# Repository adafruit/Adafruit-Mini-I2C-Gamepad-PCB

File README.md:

## Adafruit Mini I2C Gamepad with seesaw and STEMMA QT PCB

<a href="http://www.adafruit.com/products/5743"><br/>
Click here to purchase one from the Adafruit shop</a>

PCB files for the Adafruit Mini I2C Gamepad with seesaw and STEMMA QT. 

Format is EagleCAD schematic and board layout
* https://www.adafruit.com/product/5743

### Description

Make a game or robotic controller for any I2C microcontroller or microcomputer with this tiny gamepad breakout board. This design has a 2-axis thumb joystick and 6 momentary buttons (4 large and 2 small). The board communicates with your host microcontroller over I2C so it's easy to use and doesn't take up any of your precious analog or digital pins. There is also an optional interrupt pin that can alert your feather when a button has been pressed or released to free up processor time for other tasks.

You can use our Arduino library to control and read data with any compatible microcontroller. We also have CircuitPython/Python code for use with computers or single-board Linux boards.

To get you going fast, this board comes with a STEMMA QT connector, making them easy to interface with. The STEMMA QT connector is compatible with the SparkFun Qwiic I2C connectors. This allows you to make solderless connections between your development board and the gamepad or to chain it with a wide range of other sensors and accessories using a compatible cable and a 'hub' board. QT Cable is not included, but we have a variety in the shop.

This board features Adafruit seesaw technology - a custom programmed little helper microcontroller that takes the two analog inputs from the joystick, and 6 button inputs, and converts it into a pretty I2C interface. This I2C interface means you don't 'lose' any GPIO or analog inputs, and it works with any and all microcontrollers or microcomputers - even if they don't have an analog input for the thumbstick! 

If you have an I2C address conflict, or you want to connect more than one of these to a board, there are two address-select jumpers so you have 4 options of I2C addresses.

There's an optional IRQ (interrupt) line that you can use if you'd like the gamepad to let you know when a button has been pressed. Since its optional you will need to connect a separate wire for the IRQ line, or just leave it disconnected.

Comes with one assembled and programmed Gamepad, and some 0.1" header. If you aren't using Stemma QT cables, some soldering is required to attach the header for breadboarding.

### License

Adafruit invests time and resources providing this open source design, please support Adafruit and open-source hardware by purchasing products from [Adafruit](https://www.adafruit.com)!

Designed by Limor Fried/Ladyada for Adafruit Industries.

Creative Commons Attribution/Share-Alike, all text above must be included in any redistribution. 
See license.txt for additional details.

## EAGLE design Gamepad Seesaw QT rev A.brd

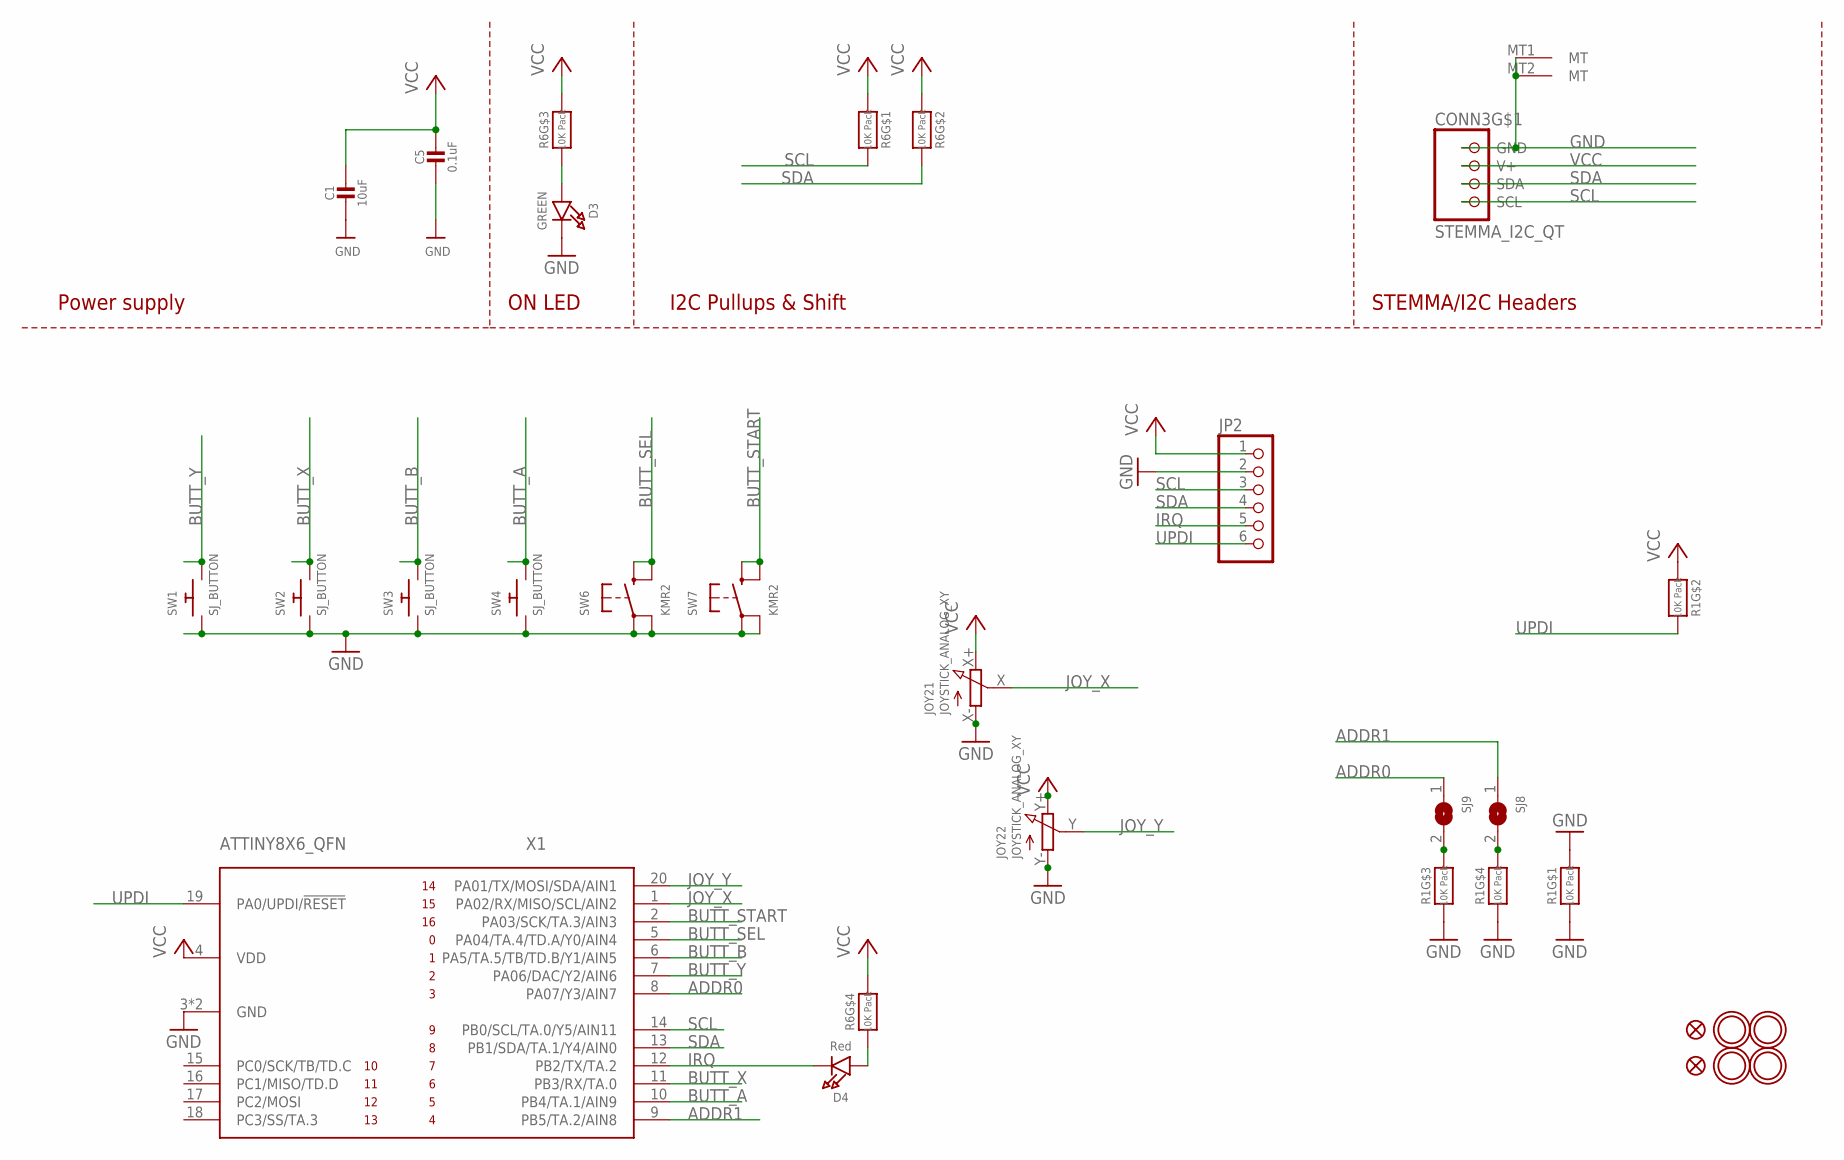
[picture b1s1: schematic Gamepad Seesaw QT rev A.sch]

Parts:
C1: 10uF; 0805-NO
C5: 0.1uF; 0603-NO
CONN3: STEMMA_I2C_QT; JST_SH4
D3: GREEN; CHIPLED_0603_NOOUTLINE
D4: Red; CHIPLED_0603_NOOUTLINE
FID1, FID2: FIDUCIAL_1MM
JOY2: JOYSTICK_ANALOG_XY; JOYSTICK_ANALOG_MINITHM
JP2: HEADER-1X6ROUND; 1X06_ROUND
R1, R6: 10K Pack; RESPACK_4X0603
SJ8, SJ9: SOLDERJUMPERCLOSED; SOLDERJUMPER_CLOSEDWIRE
SW1, SW2, SW3, SW4: SJ_BUTTON; PUSHBUTTON_SMD_SJ
SW6, SW7: KMR2; BTN_RKB2_4.6X2.8
U$1, U$2, U$3, U$4: MOUNTINGHOLE2.5; MOUNTINGHOLE_2.5_PLATED
X1: ATTINY8X6_QFN; QFN20_3MM

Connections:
ADDR0: SJ9.1, X1.8 (PA07/Y3/AIN7)
ADDR1: SJ8.1, X1.9 (PB5/TA.2/AIN8)
BUTT_A: SW4.P$2, X1.10 (PB4/TA.1/AIN9)
BUTT_B: SW3.P$2, X1.6 (PA5/TA.5/TB/TD.B/Y1/AIN5)
BUTT_SEL: SW6.B (S), SW6.B' (S1), X1.5 (PA04/TA.4/TD.A/Y0/AIN4)
BUTT_START: SW7.B (S), SW7.B' (S1), X1.2 (PA03/SCK/TA.3/AIN3)
BUTT_X: SW2.P$2, X1.11 (PB3/RX/TA.0)
BUTT_Y: SW1.P$2, X1.7 (PA06/DAC/Y2/AIN6)
GND: C1.2, C5.2, CONN3.1 (GND), CONN3.MT1 (MT), CONN3.MT2 (MT), D3.C, JOY2.X- (A), JOY2.Y- (A), JP2.2, R1.1, R1.3 (1), R1.4 (1), R1.8 (2), SW1.P$1, SW2.P$1, SW3.P$1, SW4.P$1, SW6.A, SW6.A' (P1), SW7.A, SW7.A' (P1), X1.3 (GND), X1.PAD (GND)
IRQ: D4.C, JP2.5, X1.12 (PB2/TX/TA.2)
JOY_X: JOY2.X (S), X1.1 (PA02/RX/MISO/SCL/AIN2)
JOY_Y: JOY2.Y (S), X1.20 (PA01/TX/MOSI/SDA/AIN1)
unnamed: D3.A, R6.3 (1)
unnamed: R1.6 (2), SJ9.2
unnamed: R1.5 (2), SJ8.2
unnamed: D4.A, R6.4 (1)
SCL: CONN3.4 (SCL), JP2.3, R6.8 (2), X1.14 (PB0/SCL/TA.0/Y5/AIN11)
SDA: CONN3.3 (SDA), JP2.4, R6.7 (2), X1.13 (PB1/SDA/TA.1/Y4/AIN0)
UPDI: JP2.6, R1.7 (2), X1.19 (PA0/UPDI/!RESET)
VCC: C1.1, C5.1, CONN3.2 (V+), JOY2.X+ (E), JOY2.Y+ (E), JP2.1, R1.2 (1), R6.1, R6.2 (1), R6.5 (2), R6.6 (2), X1.4 (VDD)

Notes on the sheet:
I2C Pullups & Shift
STEMMA/I2C Headers
ON LED
Power supply

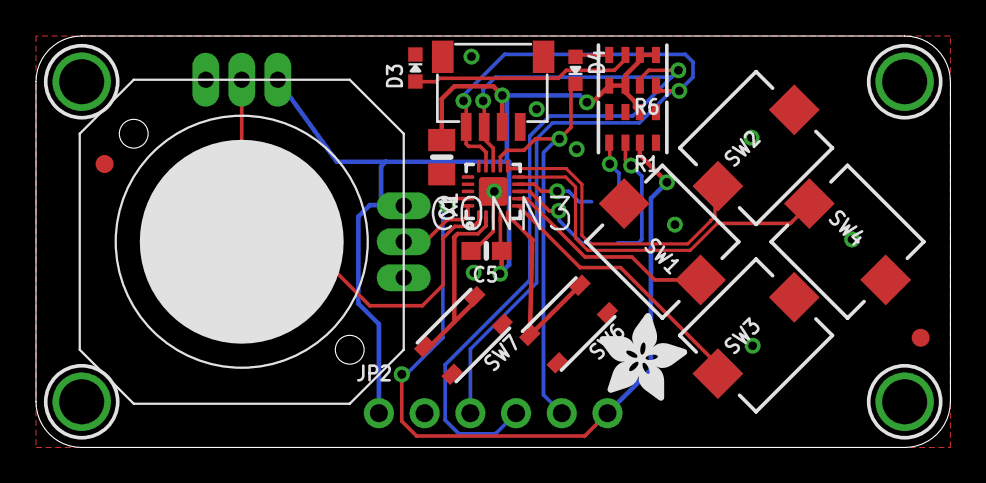
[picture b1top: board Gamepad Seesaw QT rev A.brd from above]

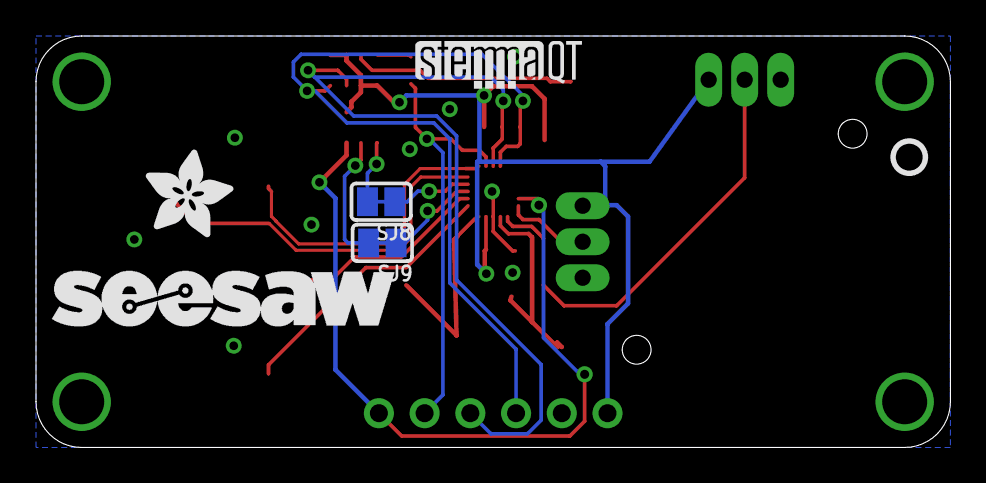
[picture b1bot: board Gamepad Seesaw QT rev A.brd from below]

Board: 2 copper layers, 50.8 x 22.9 mm, 47 parts (16 on the bottom side), 20 nets.

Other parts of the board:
PLABEL0: PLABEL0
PLABEL1: PLABEL1
PLABEL2: PLABEL2
PLABEL3: PLABEL3
PLABEL4: PLABEL4
PLABEL5: PLABEL5
PLABEL6: PLABEL6
PLABEL7: PLABEL7
PLABEL8: PLABEL8
PLABEL9: PLABEL9
PLABEL10: PLABEL10
PLABEL11: PLABEL11
PLABEL12: PLABEL12
PLABEL13: PLABEL13
PLABEL14: PLABEL14
PLABEL15: PLABEL15
PLABEL16: PLABEL16
PLABEL17: PLABEL17
U$5: STEMMAQT
U$7: PCBFEAT-REV-040
U$9, U$11: ADAFRUIT_5MM
U$12: SEESAW_LOGO

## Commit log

2023-06-26 Add board files.

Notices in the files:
parts and their libraries:
microbuilder: This work is placed in the public domain, and may be freely used for commercial and non-commercial work with the following conditions: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
